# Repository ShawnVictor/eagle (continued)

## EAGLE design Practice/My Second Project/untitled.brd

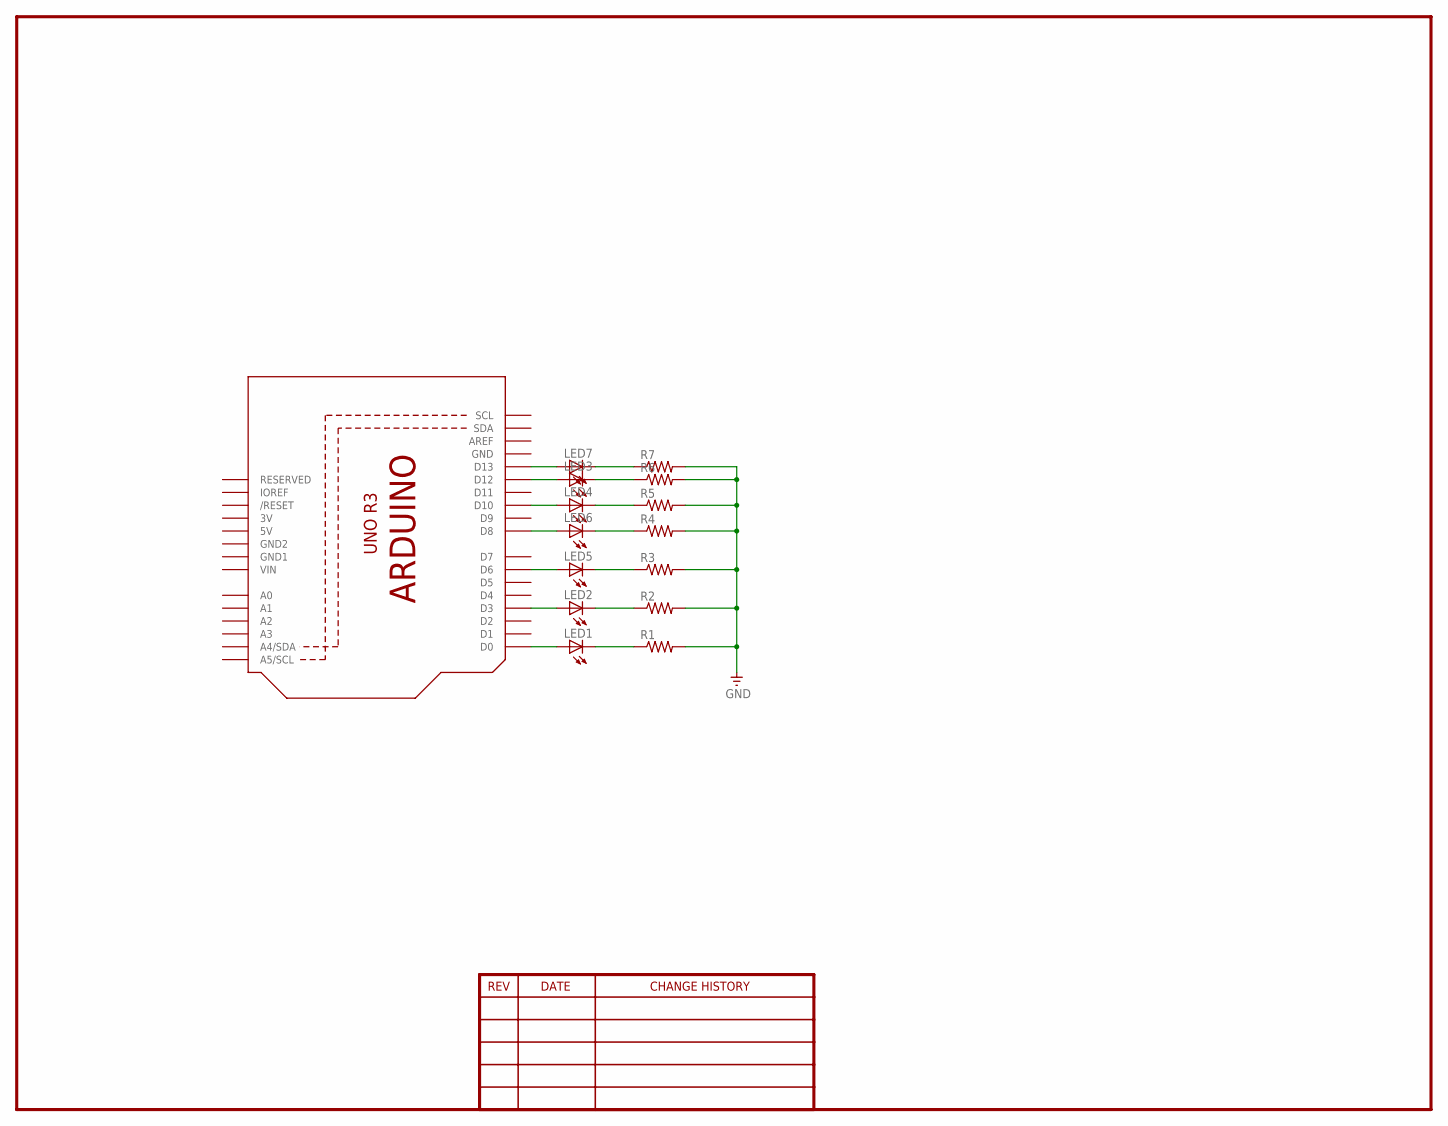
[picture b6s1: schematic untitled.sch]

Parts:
LED1: LED5MM
LED2, LED3, LED4, LED5, LED6, LED7: LEDCHIP-LED0603; CHIP-LED0603
R1: R-US_0309/12; 0309/12
R2, R3, R4, R5, R6, R7: R-US_M0805; M0805
U1: ARDUINOR3-BPLACE

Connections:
3V: U1.3V
5V: U1.5V
GND: R1.2, R2.2, R3.2, R4.2, R5.2, R6.2, R7.2, U1.GND
GND1: U1.GND1
GND2: U1.GND2
unnamed: LED1.A, U1.D0
unnamed: LED1.K (C), R1.1
unnamed: LED2.A, U1.D3
unnamed: LED5.A, U1.D6
unnamed: LED6.A, U1.D8
unnamed: LED4.A, U1.D10
unnamed: LED3.A, U1.D12
unnamed: LED7.A, U1.D13
unnamed: LED7.C, R7.1
unnamed: LED3.C, R6.1
unnamed: LED4.C, R5.1
unnamed: LED6.C, R4.1
unnamed: LED5.C, R3.1
unnamed: LED2.C, R2.1
VIN: U1.VIN

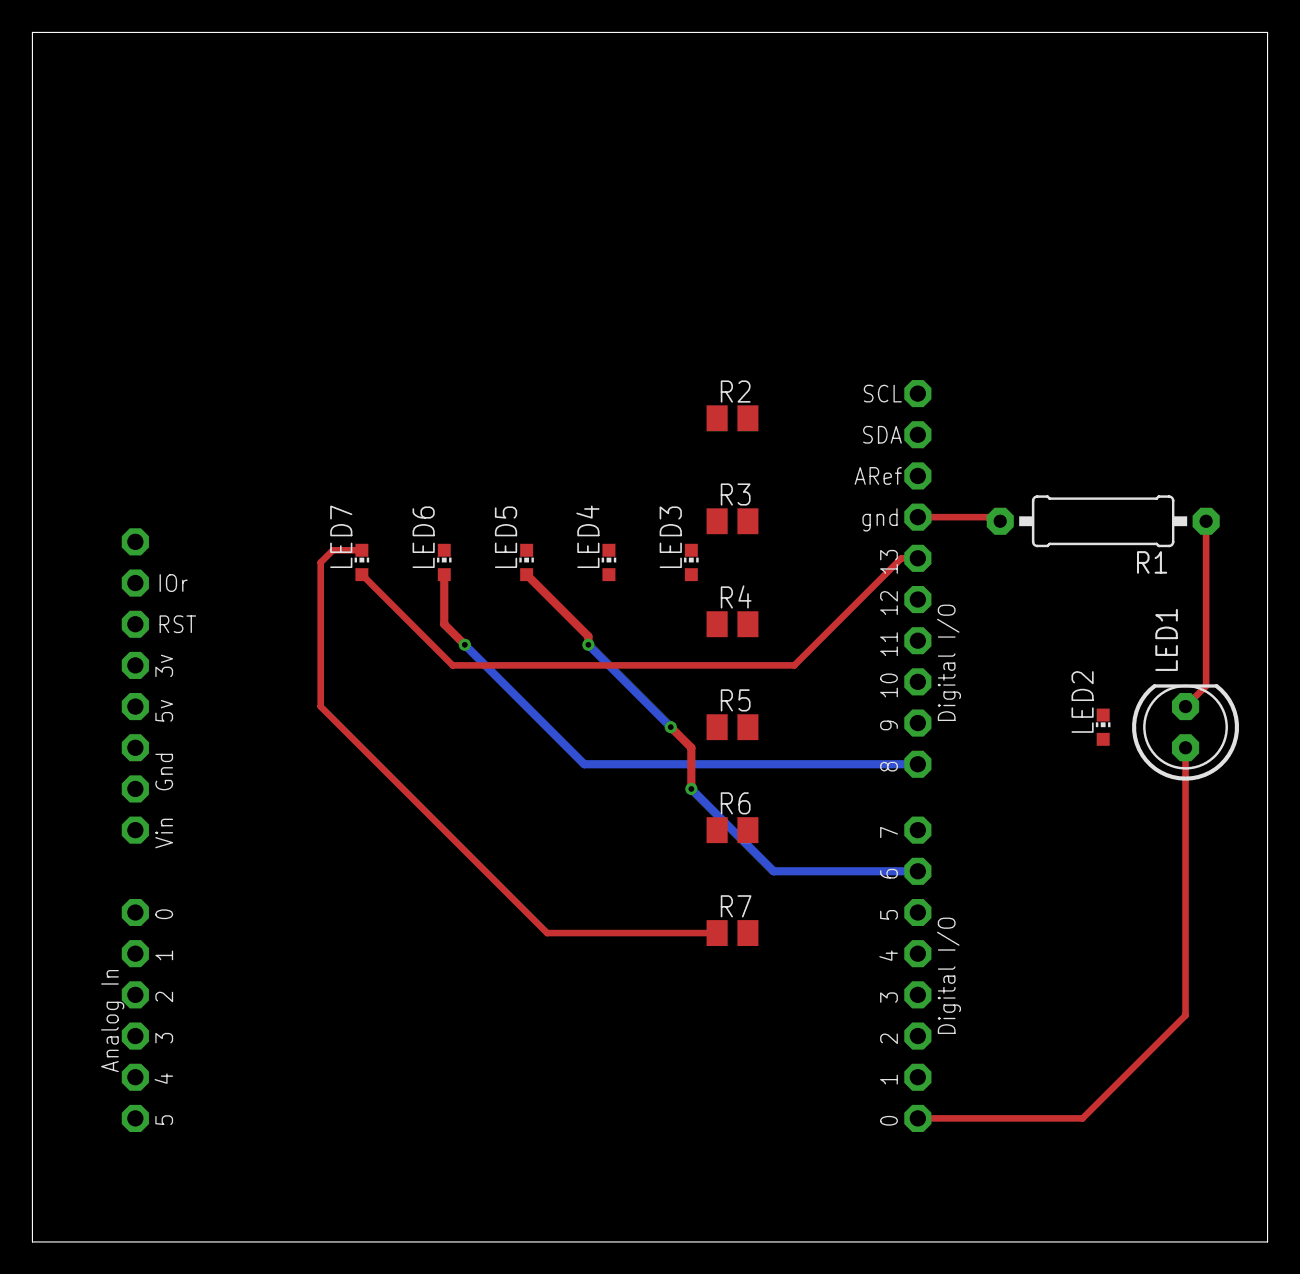
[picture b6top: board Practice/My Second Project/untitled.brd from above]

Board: 2 copper layers, 76.2 x 74.6 mm, 15 parts (0 on the bottom side), 15 nets.
